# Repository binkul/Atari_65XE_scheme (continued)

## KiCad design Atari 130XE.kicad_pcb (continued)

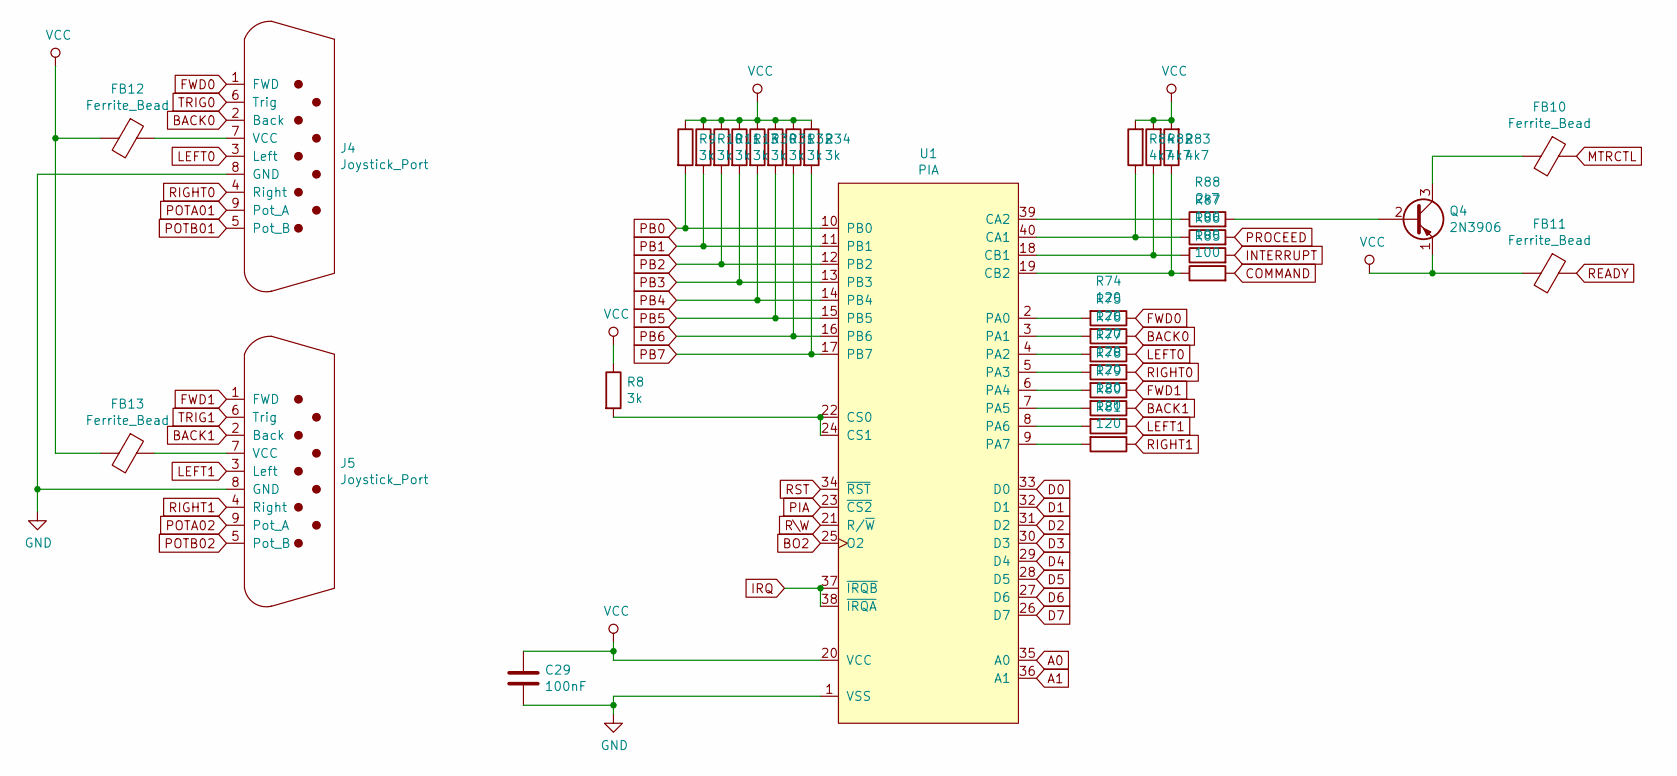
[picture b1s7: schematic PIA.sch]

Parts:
C29: 100nF; C_Disc_D5.0mm_W2.5mm_P5.00mm
FB10, FB11, FB12, FB13: Ferrite_Bead; L_Axial_L9.5mm_D4.0mm_P12.70mm_Horizontal_Fastron_SMCC
J4, J5: Joystick_Port; Joystick_Pport
Q4: 2N3906; TO-92_Inline
R8, R9, R10, R11, R13, R30, R31, R32, R34: 3k; R_1206_3216Metric_Pad1.42x1.75mm_HandSolder
R74, R75, R76, R77, R78, R79, R80, R81: 120; R_1206_3216Metric_Pad1.42x1.75mm_HandSolder
R82, R83, R84: 4k7; R_1206_3216Metric_Pad1.42x1.75mm_HandSolder
R85, R86, R87: 100; R_1206_3216Metric_Pad1.42x1.75mm_HandSolder
R88: 2k7; R_1206_3216Metric_Pad1.42x1.75mm_HandSolder
U1: PIA; DIP-40_W15.24mm_LongPads

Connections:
A0: U1.35 (A0); also elsewhere on the board
A1: U1.36 (A1); also elsewhere on the board
BACK0: J4.2 (Back), R75.1
BACK1: J5.2 (Back), R79.1
BO2: U1.25 (O2); also elsewhere on the board
COMMAND: R85.2; also elsewhere on the board
D0: U1.33 (D0); also elsewhere on the board
D1: U1.32 (D1); also elsewhere on the board
D2: U1.31 (D2); also elsewhere on the board
D3: U1.30 (D3); also elsewhere on the board
D4: U1.29 (D4); also elsewhere on the board
D5: U1.28 (D5); also elsewhere on the board
D6: U1.27 (D6); also elsewhere on the board
D7: U1.26 (D7); also elsewhere on the board
FWD0: J4.1 (FWD), R74.1
FWD1: J5.1 (FWD), R78.1
GND: C29.2, J4.8 (GND), J5.8 (GND), U1.1 (VSS); also elsewhere on the board
INTERRUPT: R86.2; also elsewhere on the board
IRQ: U1.37 (~IRQB), U1.38 (~IRQA); also elsewhere on the board
LEFT0: J4.3 (Left), R76.1
LEFT1: J5.3 (Left), R80.1
MTRCTL: FB10.1; also elsewhere on the board
unnamed: FB10.2, Q4.3 (C)
unnamed: FB12.1, J4.7 (VCC)
unnamed: FB13.1, J5.7 (VCC)
unnamed: Q4.2 (B), R88.2
unnamed: R8.2, U1.22 (CS0), U1.24 (CS1)
unnamed: R74.2, U1.2 (PA0)
unnamed: R75.2, U1.3 (PA1)
unnamed: R76.2, U1.4 (PA2)
unnamed: R77.2, U1.5 (PA3)
unnamed: R78.2, U1.6 (PA4)
unnamed: R79.2, U1.7 (PA5)
unnamed: R80.2, U1.8 (PA6)
unnamed: R81.2, U1.9 (PA7)
unnamed: R82.1, R86.1, U1.18 (CB1)
unnamed: R83.1, R85.1, U1.19 (CB2)
unnamed: R84.1, R87.1, U1.40 (CA1)
unnamed: R88.1, U1.39 (CA2)
PB0: R9.2, U1.10 (PB0); also elsewhere on the board
PB1: R10.2, U1.11 (PB1); also elsewhere on the board
PB2: R11.2, U1.12 (PB2); also elsewhere on the board
PB3: R13.2, U1.13 (PB3); also elsewhere on the board
PB4: R30.2, U1.14 (PB4); also elsewhere on the board
PB5: R31.2, U1.15 (PB5); also elsewhere on the board
PB6: R32.2, U1.16 (PB6); also elsewhere on the board
PB7: R34.2, U1.17 (PB7); also elsewhere on the board
PIA: U1.23 (~CS2); also elsewhere on the board
POTA01: J4.9 (Pot_A); also elsewhere on the board
POTA02: J5.9 (Pot_A); also elsewhere on the board
POTB01: J4.5 (Pot_B); also elsewhere on the board
POTB02: J5.5 (Pot_B); also elsewhere on the board
PROCEED: R87.2; also elsewhere on the board
READY: FB11.1; also elsewhere on the board
RIGHT0: J4.4 (Right), R77.1
RIGHT1: J5.4 (Right), R81.1
RST: U1.34 (~RST); also elsewhere on the board
R\W: U1.21 (R/~W); also elsewhere on the board
TRIG0: J4.6 (Trig); also elsewhere on the board
TRIG1: J5.6 (Trig); also elsewhere on the board
VCC: C29.1, FB11.2, FB12.2, FB13.2, Q4.1 (E), R8.1, R9.1, R10.1, R11.1, R13.1, R30.1, R31.1, R32.1, R34.1, R82.2, R83.2, R84.2, U1.20 (VCC); also elsewhere on the board

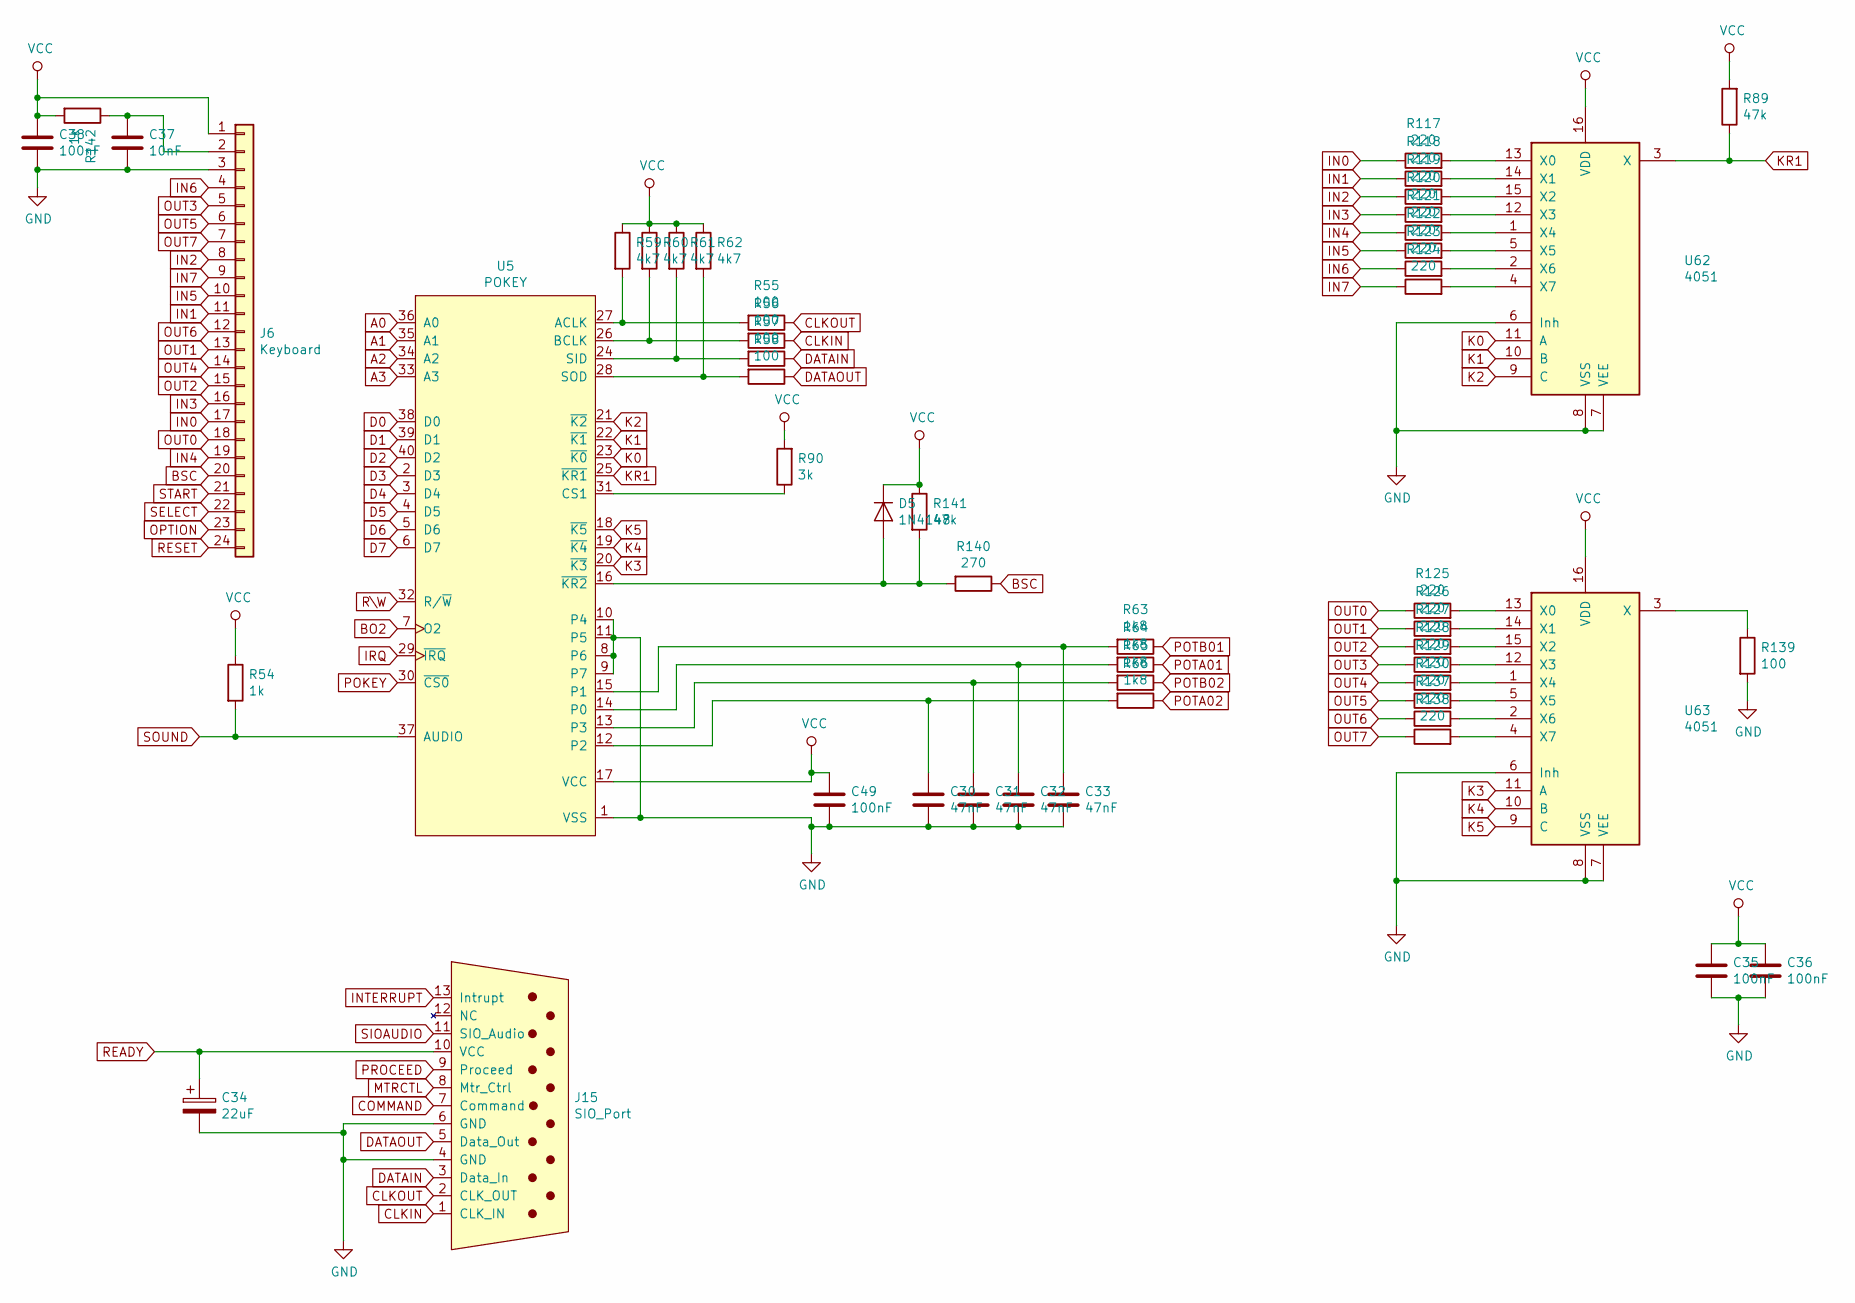
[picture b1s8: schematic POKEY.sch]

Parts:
C30, C31, C32, C33: 47nF; C_1206_3216Metric_Pad1.42x1.75mm_HandSolder
C34: 22uF; CP_Radial_D5.0mm_P2.00mm
C35, C36, C49: 100nF; C_Disc_D5.0mm_W2.5mm_P5.00mm
C37: 10nF; C_1206_3216Metric_Pad1.42x1.75mm_HandSolder
C38: 100nF; C_1206_3216Metric_Pad1.42x1.75mm_HandSolder
D5: 1N4148; D_MiniMELF_Handsoldering
J6: Keyboard; PinHeader_1x24_P2.54mm_Vertical
J15: SIO_Port; SIO_Slot
R54, R142: 1k; R_1206_3216Metric_Pad1.42x1.75mm_HandSolder
R55, R56, R57, R58, R139: 100; R_1206_3216Metric_Pad1.42x1.75mm_HandSolder
R59, R60, R61, R62: 4k7; R_1206_3216Metric_Pad1.42x1.75mm_HandSolder
R63, R64, R65, R66: 1k8; R_1206_3216Metric_Pad1.42x1.75mm_HandSolder
R89, R141: 47k; R_1206_3216Metric_Pad1.42x1.75mm_HandSolder
R90: 3k; R_1206_3216Metric_Pad1.42x1.75mm_HandSolder
R117, R118, R119, R120, R121, R122, R123, R124, R125, R126, R127, R128, R129, R130, R137, R138: 220; R_1206_3216Metric_Pad1.42x1.75mm_HandSolder
R140: 270; R_1206_3216Metric_Pad1.42x1.75mm_HandSolder
U5: POKEY; DIP-40_W15.24mm_LongPads
U62, U63: 4051; DIP-16_W7.62mm_Socket

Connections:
A0: U5.36 (A0); also elsewhere on the board
A1: U5.35 (A1); also elsewhere on the board
A2: U5.34 (A2); also elsewhere on the board
A3: U5.33 (A3); also elsewhere on the board
BO2: U5.7 (O2); also elsewhere on the board
BSC: J6.20, R140.1
CLKIN: J15.1 (CLK_IN), R56.1
CLKOUT: J15.2 (CLK_OUT), R55.1
COMMAND: J15.7 (Command); also elsewhere on the board
D0: U5.38 (D0); also elsewhere on the board
D1: U5.39 (D1); also elsewhere on the board
D2: U5.40 (D2); also elsewhere on the board
D3: U5.2 (D3); also elsewhere on the board
D4: U5.3 (D4); also elsewhere on the board
D5: U5.4 (D5); also elsewhere on the board
D6: U5.5 (D6); also elsewhere on the board
D7: U5.6 (D7); also elsewhere on the board
DATAIN: J15.3 (Data_In), R57.1
DATAOUT: J15.5 (Data_Out), R58.1
GND: C30.2, C31.2, C32.2, C33.2, C34.2, C35.2, C36.2, C37.2, C38.2, C49.2, J6.3, J15.4 (GND), J15.6 (GND), R139.2, U5.1 (VSS), U5.8 (P6), U5.9 (P7), U5.10 (P4), U5.11 (P5), U62.6 (Inh), U62.7 (VEE), U62.8 (VSS), U63.6 (Inh), U63.7 (VEE), U63.8 (VSS); also elsewhere on the board
IN0: J6.17, R117.1
IN1: J6.11, R118.1
IN2: J6.8, R119.1
IN3: J6.16, R120.1
IN4: J6.19, R121.1
IN5: J6.10, R122.1
IN6: J6.4, R123.1
IN7: J6.9, R124.1
INTERRUPT: J15.13 (Intrupt); also elsewhere on the board
IRQ: U5.29 (~IRQ); also elsewhere on the board
K0: U5.23 (~K0), U62.11 (A)
K1: U5.22 (~K1), U62.10 (B)
K2: U5.21 (~K2), U62.9 (C)
K3: U5.20 (~K3), U63.11 (A)
K4: U5.19 (~K4), U63.10 (B)
K5: U5.18 (~K5), U63.9 (C)
KR1: R89.1, U5.25 (~KR1), U62.3 (X)
MTRCTL: J15.8 (Mtr_Ctrl); also elsewhere on the board
unnamed: C30.1, R66.2, U5.12 (P2)
unnamed: C31.1, R65.2, U5.13 (P3)
unnamed: C32.1, R64.2, U5.14 (P0)
unnamed: C33.1, R63.2, U5.15 (P1)
unnamed: C37.1, J6.2, R142.1
unnamed: D5.2 (A), R140.2, R141.2, U5.16 (~KR2)
unnamed: R55.2, R59.2, U5.27 (ACLK)
unnamed: R56.2, R60.2, U5.26 (BCLK)
unnamed: R57.2, R61.2, U5.24 (SID)
unnamed: R58.2, R62.2, U5.28 (SOD)
unnamed: R90.1, U5.31 (CS1)
unnamed: R117.2, U62.13 (X0)
unnamed: R118.2, U62.14 (X1)
unnamed: R119.2, U62.15 (X2)
unnamed: R120.2, U62.12 (X3)
unnamed: R121.2, U62.1 (X4)
unnamed: R122.2, U62.5 (X5)
unnamed: R123.2, U62.2 (X6)
unnamed: R124.2, U62.4 (X7)
unnamed: R125.2, U63.13 (X0)
unnamed: R126.2, U63.14 (X1)
unnamed: R127.2, U63.15 (X2)
unnamed: R128.2, U63.12 (X3)
unnamed: R129.2, U63.1 (X4)
unnamed: R130.2, U63.5 (X5)
unnamed: R137.2, U63.2 (X6)
unnamed: R138.2, U63.4 (X7)
unnamed: R139.1, U63.3 (X)
OPTION: J6.23; also elsewhere on the board
OUT0: J6.18, R125.1
OUT1: J6.13, R126.1
OUT2: J6.15, R127.1
OUT3: J6.5, R128.1
OUT4: J6.14, R129.1
OUT5: J6.6, R130.1
OUT6: J6.12, R137.1
OUT7: J6.7, R138.1
POKEY: U5.30 (~CS0); also elsewhere on the board
POTA01: R64.1; also elsewhere on the board
POTA02: R66.1; also elsewhere on the board
POTB01: R63.1; also elsewhere on the board
POTB02: R65.1; also elsewhere on the board
PROCEED: J15.9 (Proceed); also elsewhere on the board
READY: C34.1, J15.10 (VCC); also elsewhere on the board
RESET: J6.24; also elsewhere on the board
R\W: U5.32 (R/~W); also elsewhere on the board
SELECT: J6.22; also elsewhere on the board
SIOAUDIO: J15.11 (SIO_Audio); also elsewhere on the board
SOUND: R54.2, U5.37 (AUDIO); also elsewhere on the board
START: J6.21; also elsewhere on the board
VCC: C35.1, C36.1, C38.1, C49.1, D5.1 (K), J6.1, R54.1, R59.1, R60.1, R61.1, R62.1, R89.2, R90.2, R141.1, R142.2, U5.17 (VCC), U62.16 (VDD), U63.16 (VDD); also elsewhere on the board

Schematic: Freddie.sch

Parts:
C21, C22: 27pF; C_Disc_D3.0mm_W2.0mm_P2.50mm
C23, C24, C25, C26: 100nF; C_Disc_D5.0mm_W2.5mm_P5.00mm
FB14: Ferrite_Bead_Small; L_Axial_L7.0mm_D3.3mm_P10.16mm_Horizontal_Fastron_MICC
J3: Cartridge; Cartridge_Slot
J14: Conn_01x06; PinHeader_1x06_P2.54mm_Vertical
J16: Conn_01x05; PinHeader_1x05_P2.54mm_Vertical
J17: Conn_01x04; PinHeader_1x04_P2.54mm_Vertical
R1: 3k; R_Axial_DIN0207_L3.6mm_D2.2mm_P10.16mm_Horizontal
R2, R3, R12, R114: 3k; R_1206_3216Metric_Pad1.42x1.75mm_HandSolder
R14, R15: 1k; R_1206_3216Metric_Pad1.42x1.75mm_HandSolder
R16: 240; R_Axial_DIN0207_L3.6mm_D2.2mm_P10.16mm_Horizontal
R17: 1M; R_Axial_DIN0207_L3.6mm_D2.2mm_P10.16mm_Horizontal
U9: Freddie; DIP-40_W15.24mm_LongPads
U10: 74LS08; DIP-14_W7.62mm_Socket_LongPads
U13: 74LS138; DIP-16_W7.62mm_Socket_LongPads
U14: MMU; DIP-20_W7.62mm_LongPads
Y1: 14,18757MHz; Crystal_HC18-U_Vertical

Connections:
A0: J3.5 (A0), U9.8 (A0); also elsewhere on the board
A1: J3.4 (A1), U9.9 (A1); also elsewhere on the board
A2: J3.3 (A2), U9.10 (A2); also elsewhere on the board
A3: J3.2 (A3), U9.11 (A3); also elsewhere on the board
A4: J3.C (A4), U9.12 (A4); also elsewhere on the board
A5: J3.D (A5), U9.13 (A5); also elsewhere on the board
A6: J3.E (A6), U9.14 (A6); also elsewhere on the board
A7: J3.F (A7), U9.15 (A7); also elsewhere on the board
A8: J3.H (A8), U9.16 (A8), U13.1 (A0); also elsewhere on the board
A9: J3.J (A9), U9.17 (A9), U13.2 (A1); also elsewhere on the board
A10: J3.P (A10), U9.18 (A10), U13.3 (A2); also elsewhere on the board
A11: J3.N (A11), U9.19 (A11), U14.1 (A11); also elsewhere on the board
A12: J3.K (A12), U9.21 (A12), U14.2 (A12); also elsewhere on the board
A13: U9.22 (A13), U14.3 (A13); also elsewhere on the board
A14: U14.4 (A14); also elsewhere on the board
A15: U14.5 (A15); also elsewhere on the board
BASIC: U14.13 (~BASIC); also elsewhere on the board
BE: U14.18 (~BE); also elsewhere on the board
BO2: J3.S (O2), J17.4, U10.3; also elsewhere on the board
CAS: J14.4, U9.35 (~CAS); also elsewhere on the board
CASINH: J16.3, U9.4 (~CASINH), U14.16 (~CI)
CCTL: J3.15 (~CCTL), U13.10 (O5); also elsewhere on the board
D0: J3.10 (D0); also elsewhere on the board
D1: J3.9 (D1); also elsewhere on the board
D2: J3.8 (D2); also elsewhere on the board
D3: J3.L (D3); also elsewhere on the board
D4: J3.6 (D4); also elsewhere on the board
D5: J3.7 (D5); also elsewhere on the board
D6: J3.11 (D6); also elsewhere on the board
D7: J3.M (D7); also elsewhere on the board
EXTSEL: J16.2, R1.1, U9.3 (~EXTSEL)
FA14: U9.23 (A14); also elsewhere on the board
FA15: U9.24 (A15); also elsewhere on the board
GND: C21.2, C22.2, C23.2, C24.2, C25.2, C26.2, J3.B (GND), J14.3, J16.5, J17.1, R14.1, R15.1, U9.20 (VSS), U13.5 (E2), U13.8 (GND), U14.10 (VSS); also elsewhere on the board
GTIA: U10.8; also elsewhere on the board
MAP: U14.6 (~MAP); also elsewhere on the board
MPD: R114.1, U14.14 (~MPD)
unnamed: C21.1, R16.2, Y1.1
unnamed: C22.1, J16.1, R17.2, U9.2 (CLK), Y1.2
unnamed: FB14.2, U9.40 (VCC)
unnamed: R3.1, U10.2
unnamed: R12.1, U13.6 (E3)
unnamed: R16.1, R17.1, U9.1 (CLK0)
unnamed: U10.9, U10.10, U13.15 (O0)
unnamed: U13.4 (E1), U14.17 (~IO)
O0: J17.2; also elsewhere on the board
O2: J16.4, J17.3, R2.1, U9.5 (O2), U10.1; also elsewhere on the board
OS: U14.15 (~OS); also elsewhere on the board
OSC: J14.2, U9.37 (OSC); also elsewhere on the board
PB0: U14.9 (REN); also elsewhere on the board
PIA: U13.12 (O3); also elsewhere on the board
POKEY: U13.13 (O2); also elsewhere on the board
RA0: U9.32 (RA0); also elsewhere on the board
RA1: U9.31 (RA1); also elsewhere on the board
RA2: U9.30 (RA2); also elsewhere on the board
RA3: U9.29 (RA3); also elsewhere on the board
RA4: U9.28 (RA4); also elsewhere on the board
RA5: U9.27 (RA5); also elsewhere on the board
RA6: U9.26 (RA6); also elsewhere on the board
RA7: U9.25 (RA7); also elsewhere on the board
RAS: J14.6, U9.33 (~RAS); also elsewhere on the board
RD4: J3.A (RD4), R14.2, U14.7 (RD4)
RD5: J3.14 (RDS), R15.2, U14.8 (RD5); also elsewhere on the board
REF: U14.11 (~REF); also elsewhere on the board
RST: U9.39 (RST); also elsewhere on the board
R\W: J3.R (R/~W), J14.1, U9.38 (R/~W); also elsewhere on the board
S4: J3.1 (~S4), U14.19 (~S4)
S5: J3.12 (~S5), U14.12 (~S5)
VCC: C23.1, C24.1, C25.1, C26.1, FB14.1, J3.13 (VCC), R1.2, R2.2, R3.2, R12.2, R114.2, U13.16 (VCC), U14.20 (VCC); also elsewhere on the board
WRT: J14.5, U9.34 (~WRT); also elsewhere on the board

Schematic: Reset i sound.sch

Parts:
C40, C42: 100n; C_1206_3216Metric_Pad1.42x1.75mm_HandSolder
D6: 1N4001; D_MiniMELF_Handsoldering
R91: 100; R_1206_3216Metric_Pad1.42x1.75mm_HandSolder
R92: 56k; R_1206_3216Metric_Pad1.42x1.75mm_HandSolder
R93: 470k; R_1206_3216Metric_Pad1.42x1.75mm_HandSolder
U21: NE555; DIP-8_W7.62mm_LongPads

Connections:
GND: C42.2, D6.2 (A), R93.2, U21.1 (GND); also elsewhere on the board
unnamed: C40.1, D6.1 (K), R93.1, U21.2 (TR), U21.6 (THR)
unnamed: C40.2, R91.1, R92.2
RESET: R91.2; also elsewhere on the board
RST: U21.3 (Q); also elsewhere on the board
VCC: C42.1, R92.1, U21.4 (R), U21.8 (VCC); also elsewhere on the board

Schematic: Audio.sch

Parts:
C100, C101, C102, C103: 100nF; C_Disc_D5.0mm_W2.5mm_P5.00mm
C105: 10uF; C_1812_4532Metric_Pad1.30x3.40mm_HandSolder
Q10: BC549; TO-92_Inline
R143, R144, R147: 100k; R_Axial_DIN0207_L3.6mm_D2.2mm_P10.16mm_Horizontal
R146: 10; R_Axial_DIN0207_L3.6mm_D2.2mm_P10.16mm_Horizontal
R148: 470k; R_Axial_DIN0207_L3.6mm_D2.2mm_P10.16mm_Horizontal
R149: 15k; R_Axial_DIN0207_L3.6mm_D2.2mm_P10.16mm_Horizontal

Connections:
AUDIO: C105.2; also elsewhere on the board
BELL: C103.1; also elsewhere on the board
GND: C100.1, Q10.3 (E); also elsewhere on the board
unnamed: C100.2, R146.1, R147.2
unnamed: C101.2, R143.2
unnamed: C102.2, R144.2
unnamed: C103.2, R148.2
unnamed: C105.1, Q10.1 (C), R147.1, R149.2
unnamed: Q10.2 (B), R143.1, R144.1, R148.1, R149.1
SIOAUDIO: C101.1; also elsewhere on the board
SOUND: C102.1; also elsewhere on the board
VCC: R146.2; also elsewhere on the board

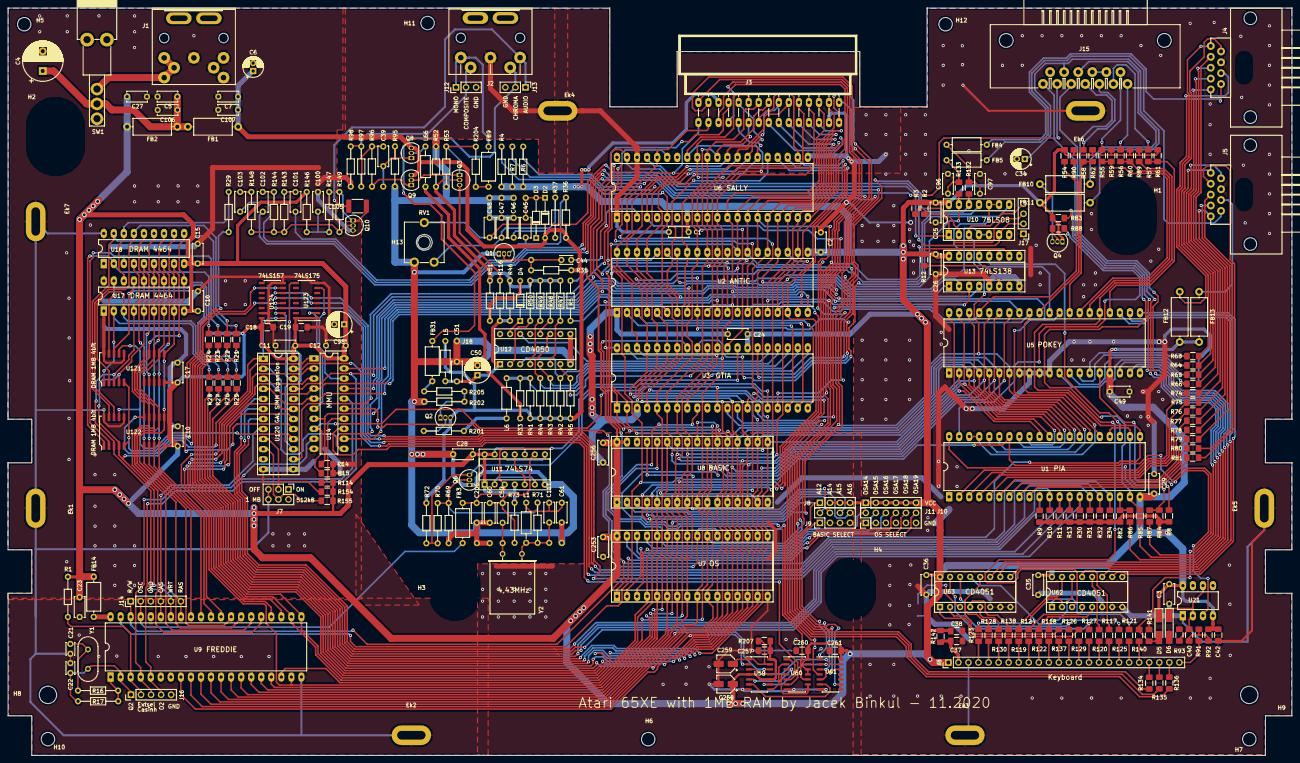
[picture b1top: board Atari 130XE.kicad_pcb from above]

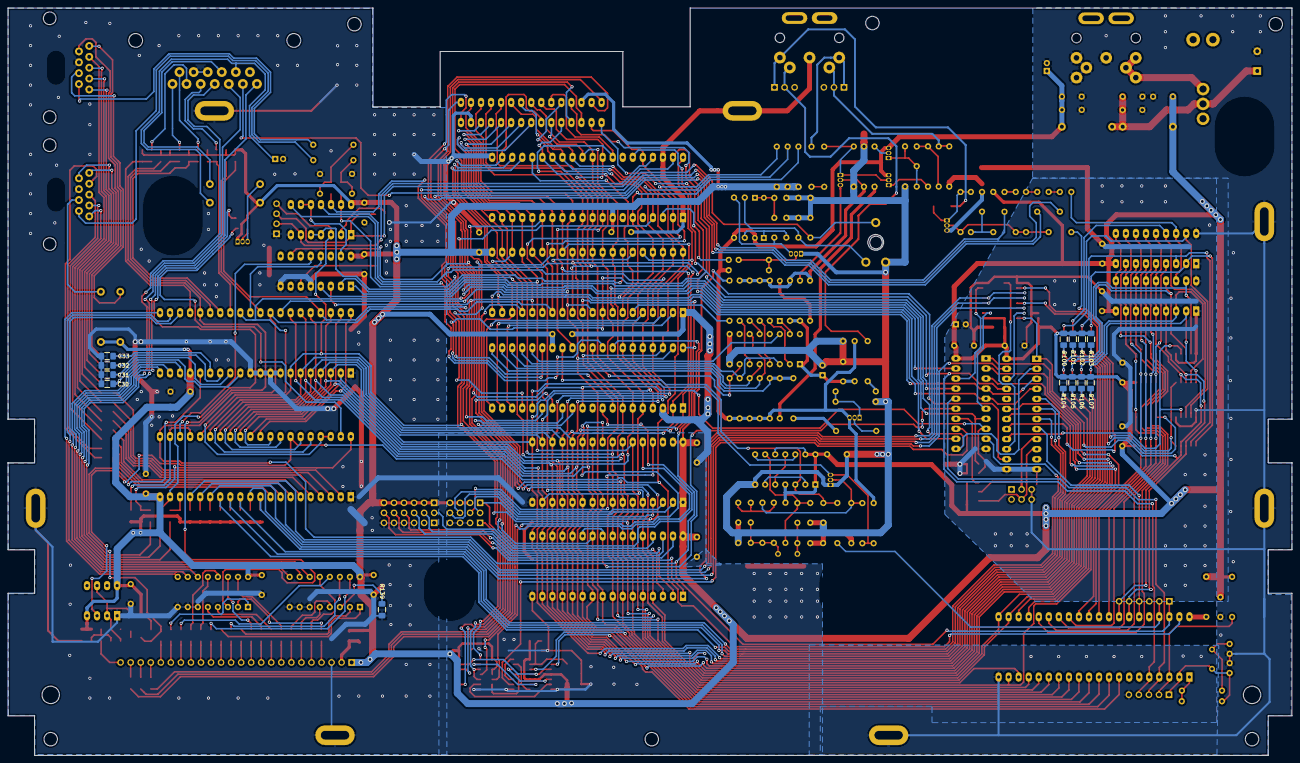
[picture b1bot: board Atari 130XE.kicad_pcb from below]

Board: 2 copper layers, 324.7 x 189.0 mm, 311 parts (13 on the bottom side), 291 nets.

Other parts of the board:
C98: 100uF; CP_Radial_D6.3mm_P2.50mm
C106, C107: 1nF; C_Disc_D5.0mm_W2.5mm_P5.00mm
C253: 100nF; C_Disc_D5.0mm_W2.5mm_P5.00mm
Ek1, Ek2, Ek3, Ek4, Ek5, Ek6, Ek7: Ekran_hole; Ekran_GND
H1, H2: MountingHole; Big_hole
H3, H4: MountingHole; Medium_hole
H5, H6, H7, H10, H11, H12: MountingHole; Hole_3.4mm
H8, H9: MountingHole; Hole_4.4mm
H13: Pot hole; MountingHole_3.2mm_M3
J10: Os Type; PinHeader_2x06_P2.54mm_Vertical
J11: Os Type; PinHeader_1x06_P2.54mm_Vertical
J12, J13: Conn_01x03; PinHeader_1x03_P2.54mm_Vertical
J18, J19, J20, J21, J22, J23, J24, J25, J26, J27, J28, J29: Pin
U7: 27C040; DIP-32_W15.24mm_Socket_LongPads

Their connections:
+5VA: C107.1; also elsewhere on the board
A0: U7.12; also elsewhere on the board
A1: U7.11; also elsewhere on the board
A2: U7.10; also elsewhere on the board
A3: U7.9; also elsewhere on the board
A4: U7.8; also elsewhere on the board
A5: U7.7; also elsewhere on the board
A6: U7.6; also elsewhere on the board
A7: U7.5; also elsewhere on the board
A8: U7.27; also elsewhere on the board
A9: U7.26; also elsewhere on the board
A10: U7.23; also elsewhere on the board
A11: U7.25; also elsewhere on the board
A12: U7.4; also elsewhere on the board
A13: U7.28; also elsewhere on the board
AUDIO: J13.1; also elsewhere on the board
CHROMA: J13.2; also elsewhere on the board
COMPOSITE: J12.2; also elsewhere on the board
D0: U7.13; also elsewhere on the board
D1: U7.14; also elsewhere on the board
D2: U7.15; also elsewhere on the board
D3: U7.17; also elsewhere on the board
D4: U7.18; also elsewhere on the board
D5: U7.19; also elsewhere on the board
D6: U7.20; also elsewhere on the board
D7: U7.21; also elsewhere on the board
GND: C98.2, C106.2, C107.2, C253.2, Ek1.1, Ek2.1, Ek3.1, Ek4.1, Ek5.1, Ek6.1, Ek7.1, J10.1, J10.3, J10.5, J10.7, J10.9, J10.11, J12.3, J13.3, J18.1, J19.1, J20.1, J22.1, J26.1, J27.1, J28.1, U7.16; also elsewhere on the board
MONO: J12.1; also elsewhere on the board
unnamed 104: J29.1; also elsewhere on the board
unnamed 108: J24.1; also elsewhere on the board
unnamed 109: J25.1; also elsewhere on the board
unnamed 115: J21.1; also elsewhere on the board
unnamed 124: C106.1; also elsewhere on the board
unnamed 125: J23.1; also elsewhere on the board
OS: U7.22, U7.24; also elsewhere on the board
OSA14: J10.2, U7.29
OSA15: J10.4, U7.3
OSA16: J10.6, U7.2
OSA17: J10.8, U7.30
OSA18: J10.10, U7.31
OSA19: J10.12, U7.1
VCC: C98.1, C253.1, J11.1, J11.2, J11.3, J11.4, J11.5, J11.6, U7.32; also elsewhere on the board

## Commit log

2020-10-25 Global rebuild up to 1mB
2020-10-28 memory track
2020-10-30 memory connection
2020-10-30 SIMM exp route
2020-10-31 Track
2020-11-01 Tracking
2020-11-03 Crystal track
2020-11-20 Track OS and Basic
2020-11-22 Finished GND
2020-11-23 Gerber
2020-11-24 Improve gerber
